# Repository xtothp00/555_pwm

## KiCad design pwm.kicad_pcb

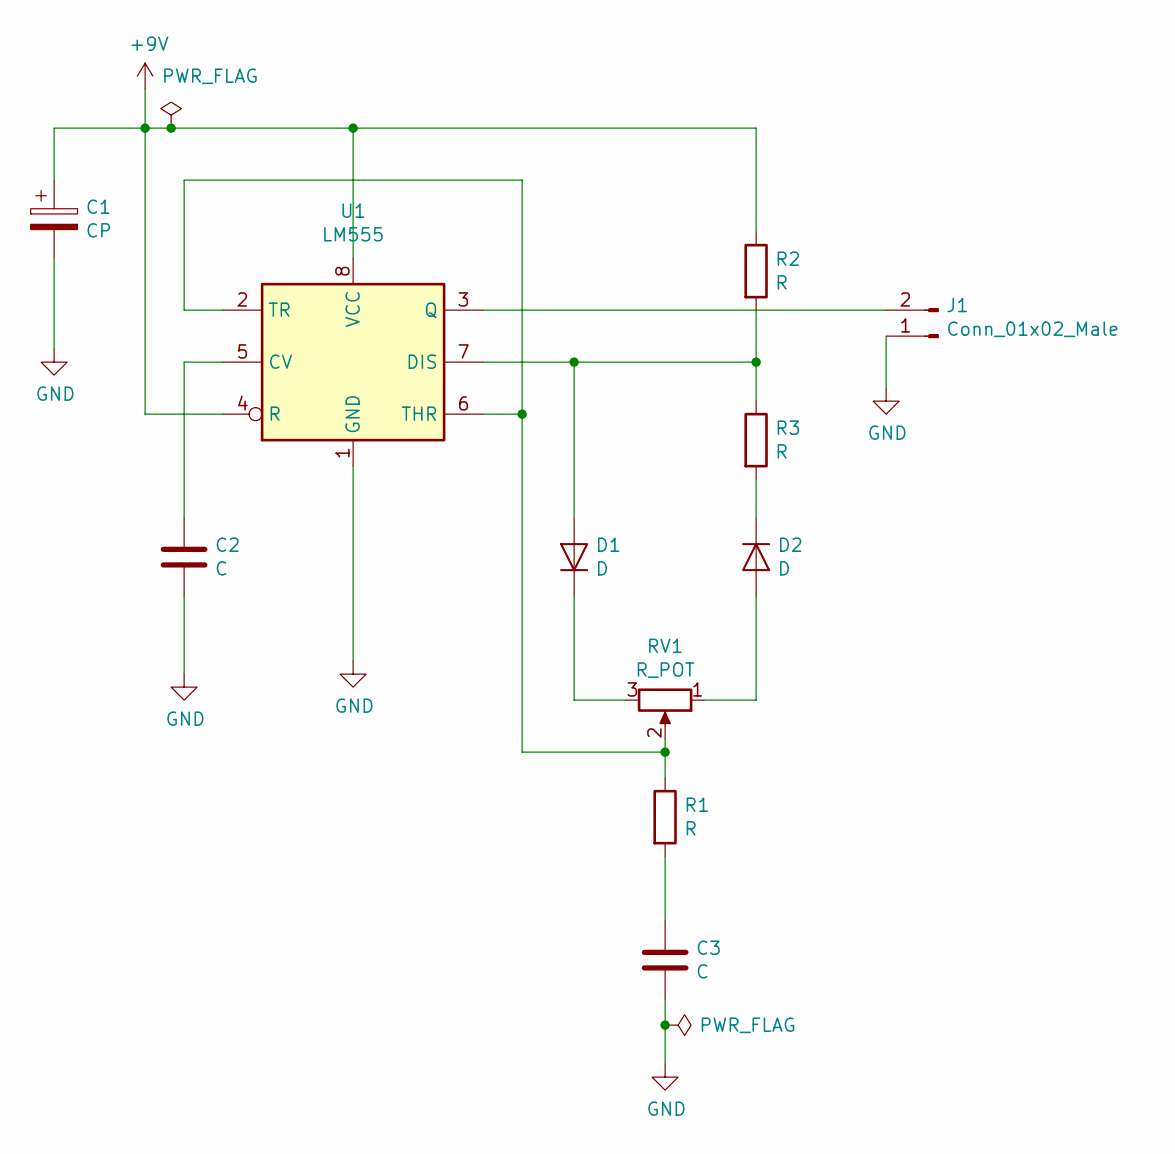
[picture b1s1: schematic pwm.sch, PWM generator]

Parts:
C1: CP; CP_EIA-3528-21_Kemet-B_Pad1.50x2.35mm_HandSolder
C2, C3: C; C_0805_2012Metric_Pad1.15x1.40mm_HandSolder
D1, D2: D; D_1210_3225Metric_Pad1.42x2.65mm_HandSolder
J1: Conn_01x02_Male; PinHeader_1x02_P2.54mm_Vertical
R1, R2, R3: R; R_0805_2012Metric_Pad1.15x1.40mm_HandSolder
RV1: R_POT; PinHeader_1x03_P2.54mm_Vertical
U1: LM555; SOIC-8_3.9x4.9mm_P1.27mm

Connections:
+9V: C1.1, R2.1, U1.4 (R), U1.8 (VCC)
GND: C1.2, C2.2, C3.2, J1.1, U1.1 (GND)
unnamed: C2.1, U1.5 (CV)
unnamed: C3.1, R1.2
unnamed: D1.1 (K), RV1.3
unnamed: D1.2 (A), R2.2, R3.1, U1.7 (DIS)
unnamed: D2.1 (K), R3.2
unnamed: D2.2 (A), RV1.1
unnamed: J1.2, U1.3 (Q)
unnamed: R1.1, RV1.2, U1.2 (TR), U1.6 (THR)

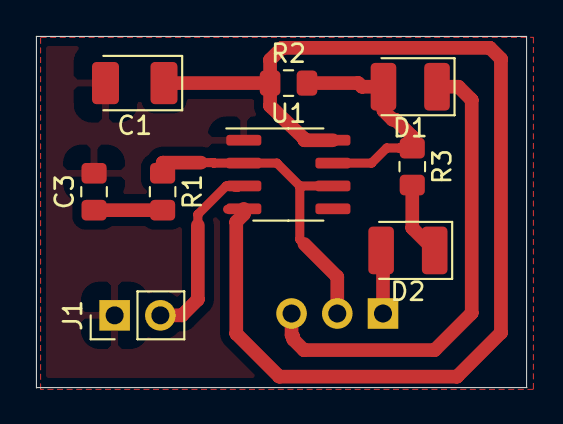
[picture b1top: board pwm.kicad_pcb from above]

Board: 2 copper layers, 27.3 x 19.5 mm, 10 parts (1 on the bottom side), 9 nets.

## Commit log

2020-01-30 Initial commit.
